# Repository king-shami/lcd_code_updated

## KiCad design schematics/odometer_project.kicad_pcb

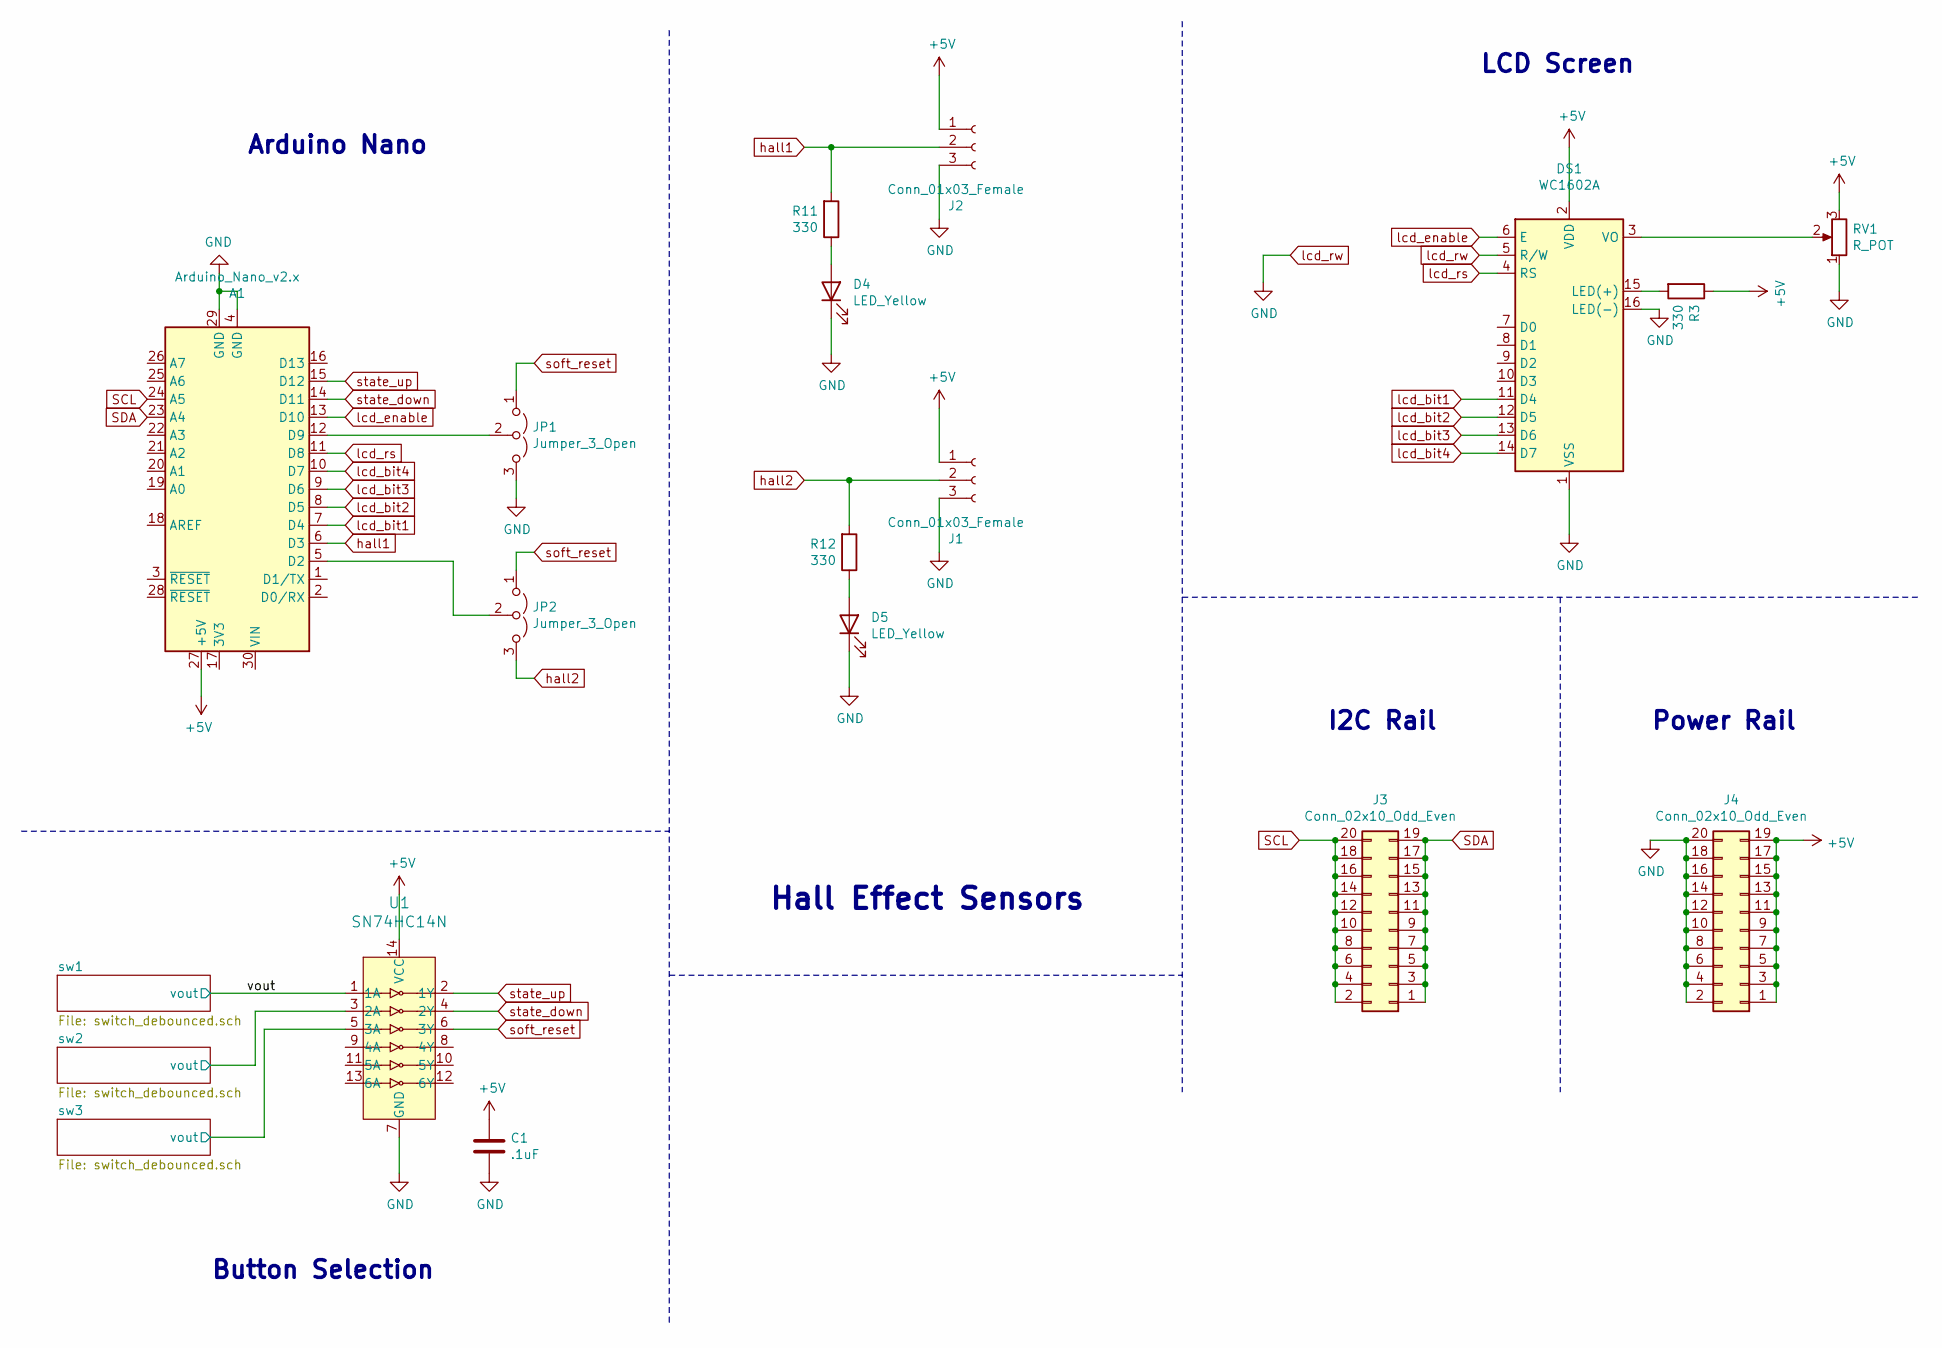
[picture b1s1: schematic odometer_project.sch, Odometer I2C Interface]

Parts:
A1: Arduino_Nano_v2.x; Arduino_Nano; Digi-Key Part Number 929974E-01-15-ND
C1: .1uF; C_0805_2012Metric_Pad1.15x1.40mm_HandSolder; LCSC Part # C49678
D4, D5: LED_Yellow; LED_0805_2012Metric_Pad1.15x1.40mm_HandSolder
DS1: WC1602A
J1, J2: Conn_01x03_Female; PinHeader_1x03_P2.54mm_Horizontal; Digi-Key Part Number 952-2245-ND
J3, J4: Conn_02x10_Odd_Even; PinHeader_2x10_P2.54mm_Vertical; Digi-Key Part Number 609-3221-ND
JP1, JP2: Jumper_3_Open; PinHeader_1x03_P2.54mm_Vertical
R3: 330; R_0805_2012Metric_Pad1.15x1.40mm_HandSolder; LCSC Part # C17630
R11, R12: 330; R_0805_2012Metric_Pad1.15x1.40mm_HandSolder
RV1: R_POT; Potentiometer_Bourns_3296W_Vertical
U1: SN74HC14N; DIP-14_W7.62mm_LongPads; MPN SN74HC14N; Digi-Key_PN 296-1577-5-ND

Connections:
+5V: A1.27 (+5V), C1.1, DS1.2 (VDD), J1.1, J2.1, J4.1, J4.3, J4.5, J4.7, J4.9, J4.11, J4.13, J4.15, J4.17, J4.19, R3.1, RV1.3, U1.14 (VCC); also elsewhere on the board
/sw2/vout: U1.3 (2A); also elsewhere on the board
/sw3/vout: U1.5 (3A); also elsewhere on the board
/vout: U1.1 (1A); also elsewhere on the board
unnamed: A1.5 (D2), JP2.2 (C)
unnamed: A1.12 (D9), JP1.2 (C)
unnamed: D4.2 (A), R11.1
unnamed: D5.2 (A), R12.1
unnamed: DS1.3 (VO), RV1.2
unnamed: DS1.15 (LED(+)), R3.2
SCL: A1.24 (A5), J3.2, J3.4, J3.6, J3.8, J3.10, J3.12, J3.14, J3.16, J3.18, J3.20
SDA: A1.23 (A4), J3.1, J3.3, J3.5, J3.7, J3.9, J3.11, J3.13, J3.15, J3.17, J3.19
hall1: A1.6 (D3), J2.2, R11.2
hall2: J1.2, JP2.3 (B), R12.2
lcd_bit1: A1.7 (D4), DS1.11 (D4)
lcd_bit2: A1.8 (D5), DS1.12 (D5)
lcd_bit3: A1.9 (D6), DS1.13 (D6)
lcd_bit4: A1.10 (D7), DS1.14 (D7)
lcd_enable: A1.13 (D10), DS1.6 (E)
lcd_rs: A1.11 (D8), DS1.4 (RS)
lcd_rw: A1.4 (GND), A1.29 (GND), C1.2, D4.1 (K), D5.1 (K), DS1.1 (VSS), DS1.5 (R/W), DS1.16 (LED(-)), J1.3, J2.3, J4.2, J4.4, J4.6, J4.8, J4.10, J4.12, J4.14, J4.16, J4.18, J4.20, JP1.3 (B), RV1.1, U1.7 (GND); also elsewhere on the board
soft_reset: JP1.1 (A), JP2.1 (A), U1.6 (3Y)
state_down: A1.14 (D11), U1.4 (2Y)
state_up: A1.15 (D12), U1.2 (1Y)

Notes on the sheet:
LCD Screen
Button Selection
I2C Rail
Power Rail
Arduino Nano
Hall Effect Sensors

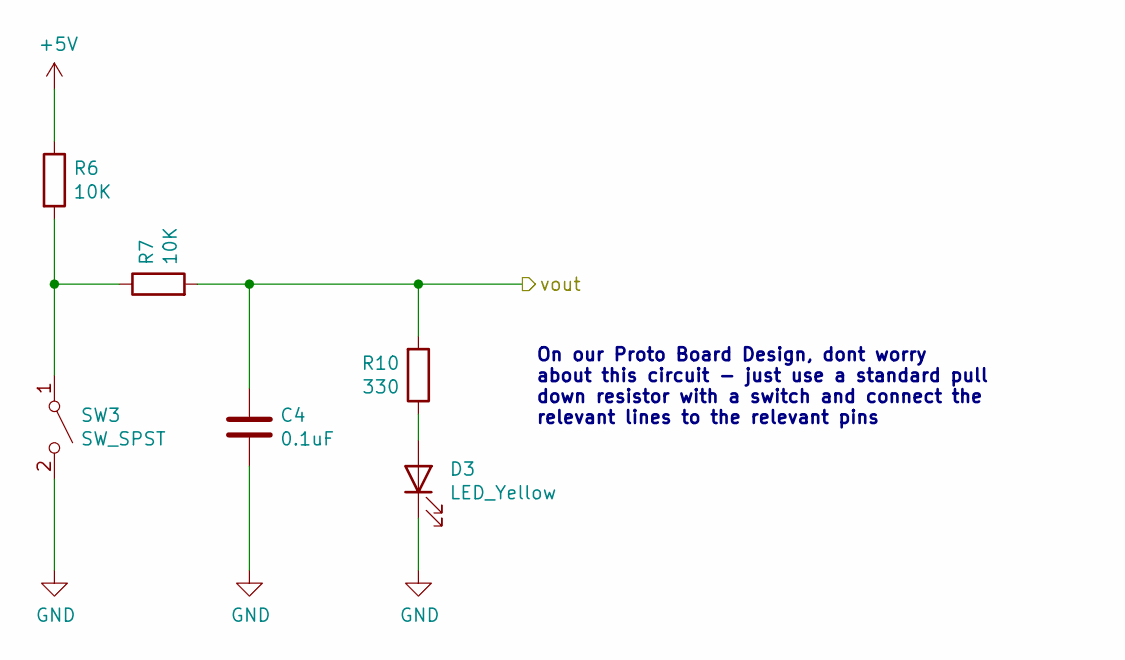
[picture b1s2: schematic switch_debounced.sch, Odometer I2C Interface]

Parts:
C2: 0.1uF; C_0805_2012Metric_Pad1.15x1.40mm_HandSolder
D1: LED_Yellow; LED_0805_2012Metric_Pad1.15x1.40mm_HandSolder
R1, R2: 10K; R_0805_2012Metric_Pad1.15x1.40mm_HandSolder
R8: 330; R_0805_2012Metric_Pad1.15x1.40mm_HandSolder
SW1: SW_SPST; SW_PUSH_6mm_H4.3mm

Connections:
+5V: R1.1; also elsewhere on the board
/vout: C2.1, R2.2, R8.2; also elsewhere on the board
unnamed: D1.2 (A), R8.1
unnamed: R1.2, R2.1, SW1.1 (A)
lcd_rw: C2.2, D1.1 (K), SW1.2 (B); also elsewhere on the board

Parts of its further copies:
C3, C4: 0.1uF; C_0805_2012Metric_Pad1.15x1.40mm_HandSolder
D2, D3: LED_Yellow; LED_0805_2012Metric_Pad1.15x1.40mm_HandSolder
R4, R5, R6, R7: 10K; R_0805_2012Metric_Pad1.15x1.40mm_HandSolder
R9, R10: 330; R_0805_2012Metric_Pad1.15x1.40mm_HandSolder
SW2, SW3: SW_SPST; SW_PUSH_6mm_H4.3mm

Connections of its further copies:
+5V: R4.1, R6.1; also elsewhere on the board
/sw2/vout: C3.1, R5.2, R9.2; also elsewhere on the board
/sw3/vout: C4.1, R7.2, R10.2; also elsewhere on the board
unnamed: D2.2 (A), R9.1
unnamed: D3.2 (A), R10.1
unnamed: R4.2, R5.1, SW2.1 (A)
unnamed: R6.2, R7.1, SW3.1 (A)
lcd_rw: C3.2, C4.2, D2.1 (K), D3.1 (K), SW2.2 (B), SW3.2 (B); also elsewhere on the board

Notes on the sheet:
On our Proto Board Design, dont worry about this circuit - just use a standard pull down resistor with a switch and connect the relevant lines to the relevant pins

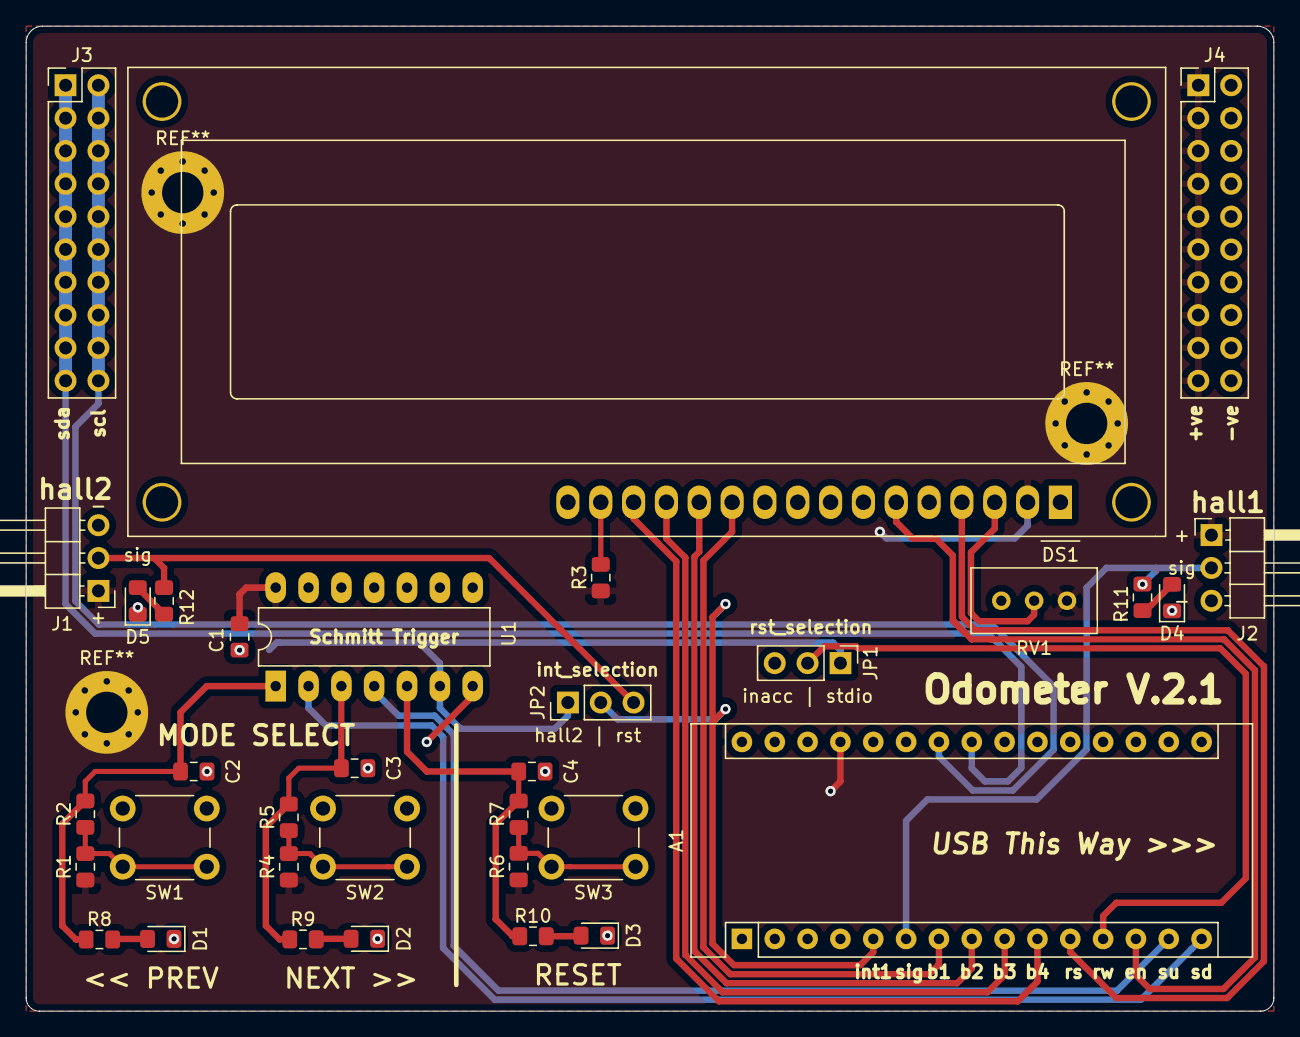
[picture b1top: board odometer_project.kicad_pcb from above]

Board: 2 copper layers, 96.5 x 76.2 mm, 34 parts (0 on the bottom side), 30 nets.

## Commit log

2020-09-30 new code
2020-09-30 working mvp
2020-09-30 hc new code"
2020-10-03 added schematic
2020-10-03 changed schematic folder
2020-10-03 fixed lcd pin connections and xtra halls
2020-10-03 added schematic notes
2020-10-05 added three button functionality
2020-10-17 production build
2020-10-19 final upload
2020-10-22 fixed velocity problem
2020-10-22 cleanup
2020-10-22 fixed issue - overflow fix
2020-10-22 removed shitty code
